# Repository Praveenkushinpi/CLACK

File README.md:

#  Thanks to HIGHWAY

```
 ________  ___       ________  ________  ___  __       
|\   ____\|\  \     |\   __  \|\   ____\|\  \|\  \     
\ \  \___|\ \  \    \ \  \|\  \ \  \___|\ \  \/  /|_   
 \ \  \    \ \  \    \ \   __  \ \  \    \ \   ___  \  
  \ \  \____\ \  \____\ \  \ \  \ \  \____\ \  \\ \  \ 
   \ \_______\ \_______\ \__\ \__\ \_______\ \__\\ \__\
    \|_______|\|_______|\|__|\|__|\|_______|\|__| \|__|

```

#  Clack — A Custom Mechanical Keyboard Build

Clack is a personal mechanical keyboard build crafted with a balance of sound, feel, and function — all under a budget of $150. Designed for a smooth typing experience and a clean aesthetic, Clack is as much a daily driver as it is a passion project.

---

##  Inspiration

The name **Clack** comes from the satisfying sound of tactile switches meeting carefully tuned stabilizers. Built for comfort and customizability, this keyboard is a love letter to DIY mechanical keyboard culture.

---

##  Build Overview

| Component     | Model/Brand               | Notes                          |
|---------------|----------------------------|--------------------------------|
| **Case**       | [Case](https://github.com/Praveenkushinpi/CLACK/tree/main/CASE)         | Material Plastic |
| **PCB**        | [PCB](https://github.com/Praveenkushinpi/CLACK/tree/main/PCB)          | Hot-swappable      |
| **Switches**   | [StacksKB](https://stackskb.com/store/akko-creamy-cyan-switch-pack-of-45-pre-order/)       | Soft/Clicky           |
| **Keycaps**    | [StacksKB](https://stackskb.com/store/wild-goose-keycaps/)         | Good              |

---

##  BOM

| Component     | Model/Brand               | Price                          |
|---------------|----------------------------|--------------------------------|
| **KeyCaps**       | [StacksKB](https://stackskb.com/store/akko-clear-white-keycap-set-v2-asa-profile/)         | 3999 inr = 50 usd |
| **Switches**        | [StacksKB](https://stackskb.com/store/akko-v3-crystal-pro-switch-pack-of-45/)          | 2999 inr = 35 usd       |
| **PCB**   | [JLCPCB](https://private-user-images.githubusercontent.com/168343716/456092456-044b7599-4a6e-40b4-bf12-a81c29c08c88.png?jwt=eyJhbGciOiJIUzI1NiIsInR5cCI6IkpXVCJ9.eyJpc3MiOiJnaXRodWIuY29tIiwiYXVkIjoicmF3LmdpdGh1YnVzZXJjb250ZW50LmNvbSIsImtleSI6ImtleTUiLCJleHAiOjE3NTA4MTkwNTksIm5iZiI6MTc1MDgxODc1OSwicGF0aCI6Ii8xNjgzNDM3MTYvNDU2MDkyNDU2LTA0NGI3NTk5LTRhNmUtNDBiNC1iZjEyLWE4MWMyOWMwOGM4OC5wbmc_WC1BbXotQWxnb3JpdGhtPUFXUzQtSE1BQy1TSEEyNTYmWC1BbXotQ3JlZGVudGlhbD1BS0lBVkNPRFlMU0E1M1BRSzRaQSUyRjIwMjUwNjI1JTJGdXMtZWFzdC0xJTJGczMlMkZhd3M0X3JlcXVlc3QmWC1BbXotRGF0ZT0yMDI1MDYyNVQwMjMyMzlaJlgtQW16LUV4cGlyZXM9MzAwJlgtQW16LVNpZ25hdHVyZT05ZDljN2U2ZmYwODhlZGU2OTJjNWVkYzk5MDk5ZWU5ODViZTY4NGQ2ZmY0Y2EyOGE5MThlMDdhMTg2MDMwMDdiJlgtQW16LVNpZ25lZEhlYWRlcnM9aG9zdCJ9.TJexbJ2JOPTNS0pWK4Fx8X82fOrmfui8mHUvjtpRxs8)       | 33 usd            |
| **Encoder**| [Robu.in](https://private-user-images.githubusercontent.com/168343716/456093939-859af2b1-9a2c-4d81-b4bb-97766db01e42.png?jwt=eyJhbGciOiJIUzI1NiIsInR5cCI6IkpXVCJ9.eyJpc3MiOiJnaXRodWIuY29tIiwiYXVkIjoicmF3LmdpdGh1YnVzZXJjb250ZW50LmNvbSIsImtleSI6ImtleTUiLCJleHAiOjE3NTA4MTkwNTksIm5iZiI6MTc1MDgxODc1OSwicGF0aCI6Ii8xNjgzNDM3MTYvNDU2MDkzOTM5LTg1OWFmMmIxLTlhMmMtNGQ4MS1iNGJiLTk3NzY2ZGIwMWU0Mi5wbmc_WC1BbXotQWxnb3JpdGhtPUFXUzQtSE1BQy1TSEEyNTYmWC1BbXotQ3JlZGVudGlhbD1BS0lBVkNPRFlMU0E1M1BRSzRaQSUyRjIwMjUwNjI1JTJGdXMtZWFzdC0xJTJGczMlMkZhd3M0X3JlcXVlc3QmWC1BbXotRGF0ZT0yMDI1MDYyNVQwMjMyMzlaJlgtQW16LUV4cGlyZXM9MzAwJlgtQW16LVNpZ25hdHVyZT1iMjA1NjJkOTMwMDA1N2Q3Yjk3ZTg1NjQ1ODc0OTgwYmY4NDY5NWFmMGJjYzkwMTY2NjUyZDFiYjYzNjExNmUxJlgtQW16LVNpZ25lZEhlYWRlcnM9aG9zdCJ9.BMnRanZ30tjBzOlprUQU22twroIURjnTTjO-QSRDdCs)  | 1 usd              |
| **Display**  | [Robu.in](https://private-user-images.githubusercontent.com/168343716/456094220-fea9dac9-632d-493f-b6a2-2cf06fdc8523.png?jwt=eyJhbGciOiJIUzI1NiIsInR5cCI6IkpXVCJ9.eyJpc3MiOiJnaXRodWIuY29tIiwiYXVkIjoicmF3LmdpdGh1YnVzZXJjb250ZW50LmNvbSIsImtleSI6ImtleTUiLCJleHAiOjE3NTA4MTkwNTksIm5iZiI6MTc1MDgxODc1OSwicGF0aCI6Ii8xNjgzNDM3MTYvNDU2MDk0MjIwLWZlYTlkYWM5LTYzMmQtNDkzZi1iNmEyLTJjZjA2ZmRjODUyMy5wbmc_WC1BbXotQWxnb3JpdGhtPUFXUzQtSE1BQy1TSEEyNTYmWC1BbXotQ3JlZGVudGlhbD1BS0lBVkNPRFlMU0E1M1BRSzRaQSUyRjIwMjUwNjI1JTJGdXMtZWFzdC0xJTJGczMlMkZhd3M0X3JlcXVlc3QmWC1BbXotRGF0ZT0yMDI1MDYyNVQwMjMyMzlaJlgtQW16LUV4cGlyZXM9MzAwJlgtQW16LVNpZ25hdHVyZT03NzIxYWFlODJjOTZiZWYwY2E0NmZmZGJmMmQwNjM2NDA0ZjEzMjBmODQ1ZTkyZTU0YzNjNGMyYWIyODY4YmJmJlgtQW16LVNpZ25lZEhlYWRlcnM9aG9zdCJ9.4TZm8LEaH7tvJQlJOL3LapiQ1uNSj3NfFEgdTf9ja4k)    | 3 usd            |

---

##  Features

- Split Keyboard
- must have 1 knobs
- a led screen
- work for both mac and windows devices
- Hot swappable 

---

##  Build Log / Showcase

---

##  Future Plans

- Swap to silent linear switches for nighttime use  
- Design custom keycap set with a "Clack" theme  
- Integrate rotary encoder or OLED screen
- Also planning to work on the split deisgn
---

##   Thanks to HIGHWAY

---

---

> “Clack is not just a sound — it's a feeling.”

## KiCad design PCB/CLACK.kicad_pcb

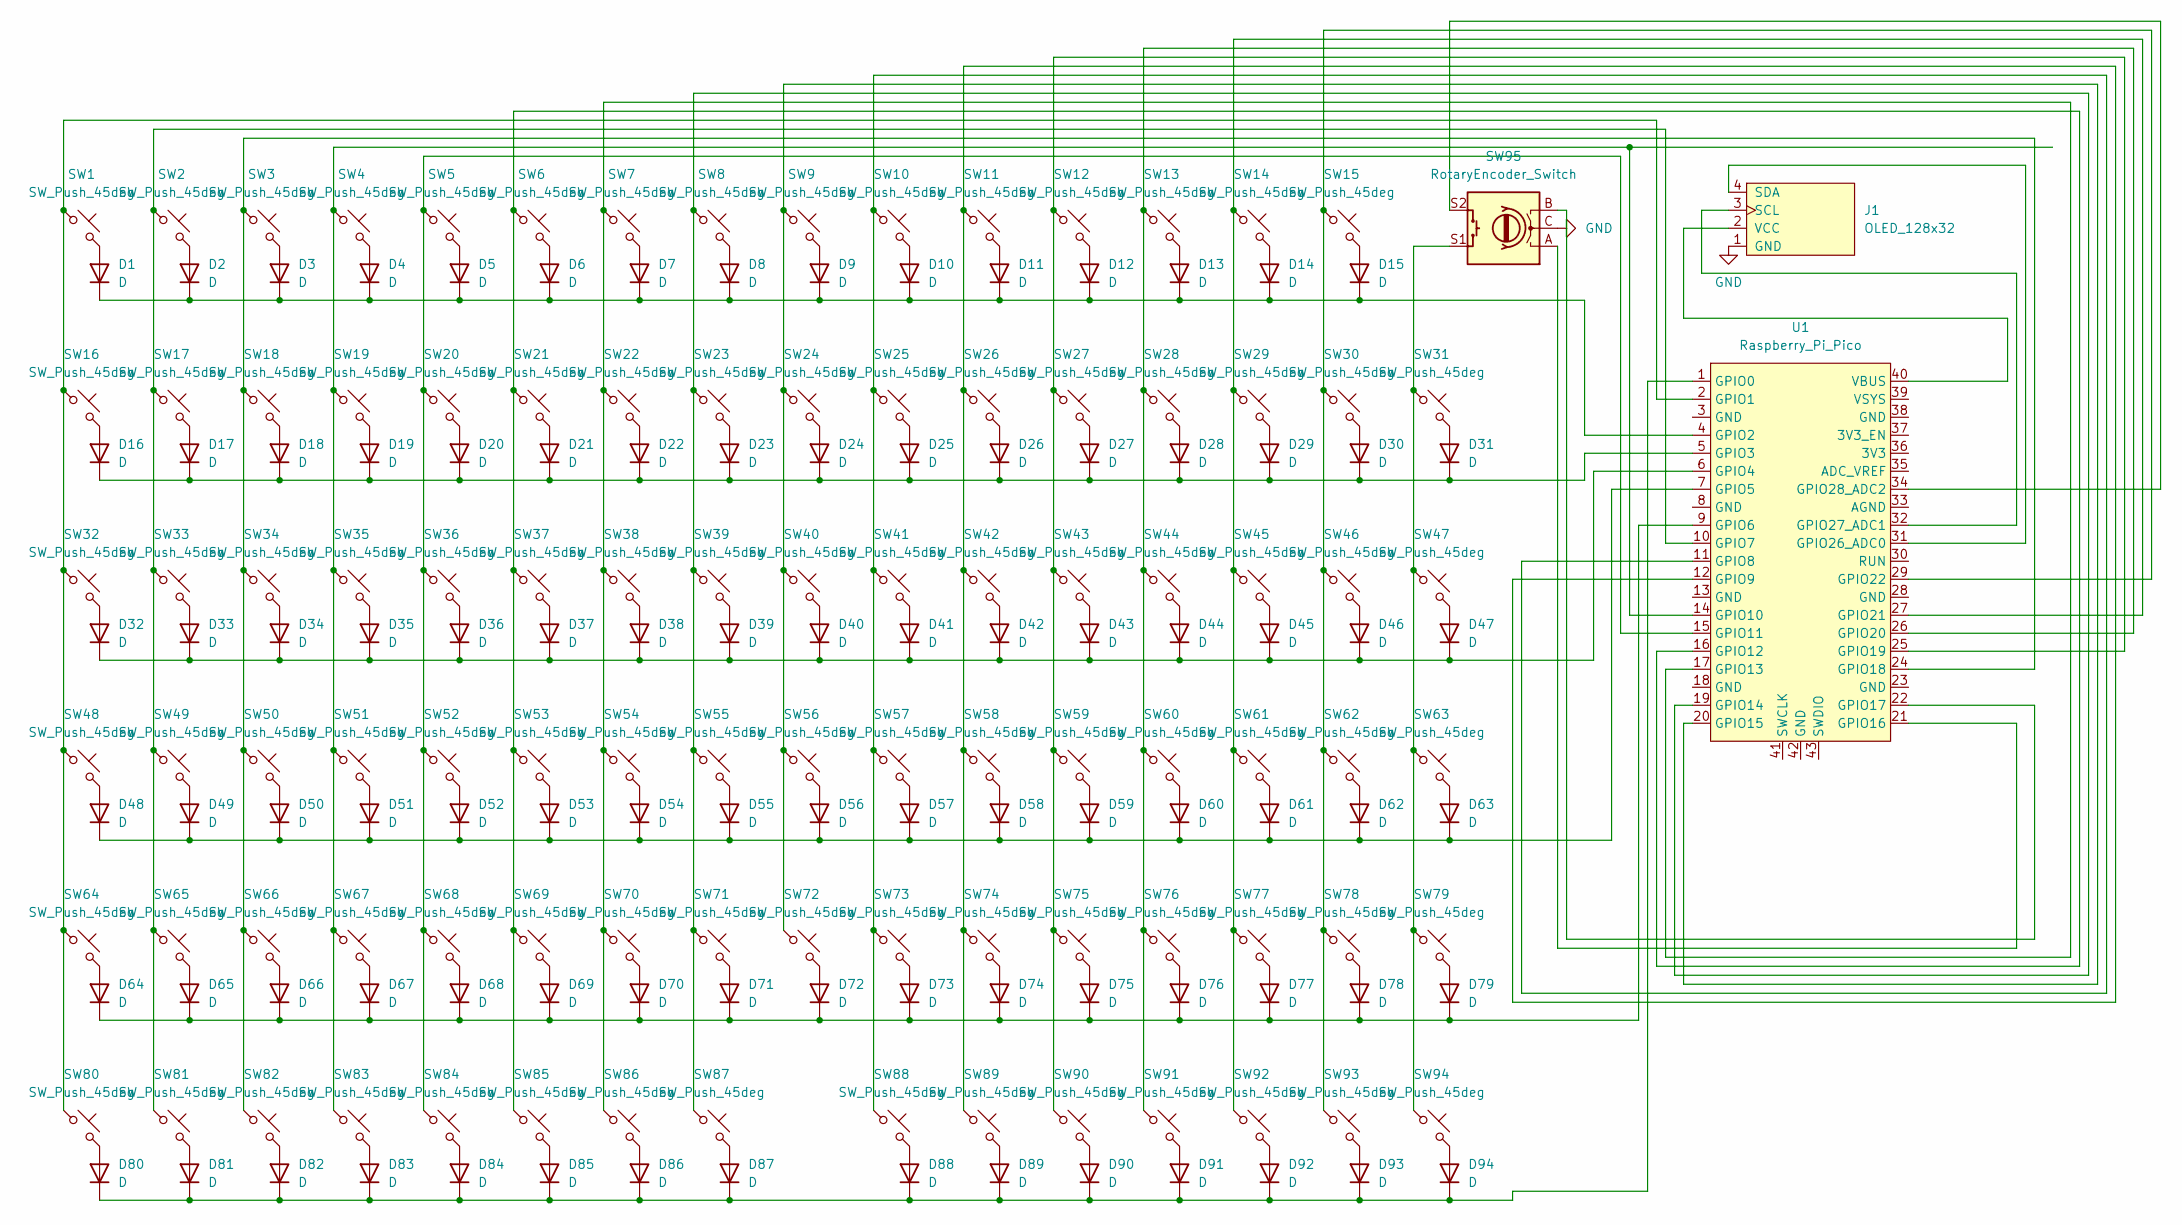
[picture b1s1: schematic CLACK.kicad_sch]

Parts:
D1, D2, D3, D4, D5, D6, D7, D8, D9, D10, D11, D12, D13, D14, D15, D16, D17, D18, D19, D20, D21, D22, D23, D24, D25, D26, D27, D28, D29, D30, D31, D32, D33, D34, D35, D36, D37, D38, D39, D40, D41, D42, D43, D44, D45, D46, D47, D48, D49, D50, D51, D52, D53, D54, D55, D56, D57, D58, D59, D60, D61, D62, D63, D64, D65, D66, D67, D68, D69, D70, D71, D72, D73, D74, D75, D76, D77, D78, D79, D80, D81, D82, D83, D84, D85, D86, D87, D88, D89, D90, D91, D92, D93, D94: D; Diode_SOD-123
J1: OLED_128x32
SW1, SW2, SW3, SW4, SW5, SW6, SW7, SW8, SW9, SW10, SW11, SW16, SW17, SW18, SW19, SW21, SW22, SW23, SW24, SW26, SW27, SW28, SW29, SW31, SW32, SW33, SW34, SW36, SW37, SW38, SW39, SW41, SW42, SW43, SW44, SW46, SW47, SW48, SW49, SW51, SW52, SW53, SW54, SW55, SW56, SW57, SW58, SW59, SW60, SW61, SW62, SW63, SW64, SW65, SW66, SW67, SW68, SW73, SW74, SW75, SW76, SW77, SW78, SW79, SW80, SW81, SW82, SW83, SW84, SW85, SW86, SW87, SW88, SW89, SW90, SW91, SW92, SW93, SW94: SW_Push_45deg; Hotswap_MX_1.00u
SW12, SW70: SW_Push_45deg; Hotswap_MX_1.50u
SW13: SW_Push_45deg; Hotswap_MX_1.75u
SW14, SW71: SW_Push_45deg; Hotswap_MX_2.25u
SW15, SW20, SW25, SW35, SW40, SW45, SW50: SW_Push_45deg; Hotswap_MX_1.25u
SW30: SW_Push_45deg; Hotswap_MX_6.25u
SW69: SW_Push_45deg; Hotswap_MX_2.00u
SW72: SW_Push_45deg; Hotswap_MX_2.75u
SW95: RotaryEncoder_Switch; RotaryEncoder_Alps_EC11E-Switch_Vertical_H20mm
U1: Raspberry_Pi_Pico

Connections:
GND: J1.1 (GND), SW95.C
unnamed: D1.2 (A), SW1.2
unnamed: D1.1 (K), D2.1 (K), D3.1 (K), D4.1 (K), D5.1 (K), D6.1 (K), D7.1 (K), D8.1 (K), D9.1 (K), D10.1 (K), D11.1 (K), D12.1 (K), D13.1 (K), D14.1 (K), D15.1 (K), U1.4 (GPIO2)
unnamed: D2.2 (A), SW2.2
unnamed: D3.2 (A), SW3.2
unnamed: D4.2 (A), SW4.2
unnamed: D5.2 (A), SW5.2
unnamed: D6.2 (A), SW6.2
unnamed: D7.2 (A), SW7.2
unnamed: D8.2 (A), SW8.2
unnamed: D9.2 (A), SW9.2
unnamed: D10.2 (A), SW10.2
unnamed: D11.2 (A), SW11.2
unnamed: D12.2 (A), SW12.2
unnamed: D13.2 (A), SW13.2
unnamed: D14.2 (A), SW14.2
unnamed: D15.2 (A), SW15.2
unnamed: D16.2 (A), SW16.2
unnamed: D16.1 (K), D17.1 (K), D18.1 (K), D19.1 (K), D20.1 (K), D21.1 (K), D22.1 (K), D23.1 (K), D24.1 (K), D25.1 (K), D26.1 (K), D27.1 (K), D28.1 (K), D29.1 (K), D30.1 (K), D31.1 (K), U1.5 (GPIO3)
unnamed: D17.2 (A), SW17.2
unnamed: D18.2 (A), SW18.2
unnamed: D19.2 (A), SW19.2
unnamed: D20.2 (A), SW20.2
unnamed: D21.2 (A), SW21.2
unnamed: D22.2 (A), SW22.2
unnamed: D23.2 (A), SW23.2
unnamed: D24.2 (A), SW24.2
unnamed: D25.2 (A), SW25.2
unnamed: D26.2 (A), SW26.2
unnamed: D27.2 (A), SW27.2
unnamed: D28.2 (A), SW28.2
unnamed: D29.2 (A), SW29.2
unnamed: D30.2 (A), SW30.2
unnamed: D31.2 (A), SW31.2
unnamed: D32.2 (A), SW32.2
unnamed: D32.1 (K), D33.1 (K), D34.1 (K), D35.1 (K), D36.1 (K), D37.1 (K), D38.1 (K), D39.1 (K), D40.1 (K), D41.1 (K), D42.1 (K), D43.1 (K), D44.1 (K), D45.1 (K), D46.1 (K), D47.1 (K), U1.6 (GPIO4)
unnamed: D33.2 (A), SW33.2
unnamed: D34.2 (A), SW34.2
unnamed: D35.2 (A), SW35.2
unnamed: D36.2 (A), SW36.2
unnamed: D37.2 (A), SW37.2
unnamed: D38.2 (A), SW38.2
unnamed: D39.2 (A), SW39.2
unnamed: D40.2 (A), SW40.2
unnamed: D41.2 (A), SW41.2
unnamed: D42.2 (A), SW42.2
unnamed: D43.2 (A), SW43.2
unnamed: D44.2 (A), SW44.2
unnamed: D45.2 (A), SW45.2
unnamed: D46.2 (A), SW46.2
unnamed: D47.2 (A), SW47.2
unnamed: D48.2 (A), SW48.2
unnamed: D48.1 (K), D49.1 (K), D50.1 (K), D51.1 (K), D52.1 (K), D53.1 (K), D54.1 (K), D55.1 (K), D56.1 (K), D57.1 (K), D58.1 (K), D59.1 (K), D60.1 (K), D61.1 (K), D62.1 (K), D63.1 (K), U1.7 (GPIO5)
unnamed: D49.2 (A), SW49.2
unnamed: D50.2 (A), SW50.2
unnamed: D51.2 (A), SW51.2
unnamed: D52.2 (A), SW52.2
unnamed: D53.2 (A), SW53.2
unnamed: D54.2 (A), SW54.2
unnamed: D55.2 (A), SW55.2
unnamed: D56.2 (A), SW56.2
unnamed: D57.2 (A), SW57.2
unnamed: D58.2 (A), SW58.2
unnamed: D59.2 (A), SW59.2
unnamed: D60.2 (A), SW60.2
unnamed: D61.2 (A), SW61.2
unnamed: D62.2 (A), SW62.2
unnamed: D63.2 (A), SW63.2
unnamed: D64.2 (A), SW64.2
unnamed: D64.1 (K), D65.1 (K), D66.1 (K), D67.1 (K), D68.1 (K), D69.1 (K), D70.1 (K), D71.1 (K), D72.1 (K), D73.1 (K), D74.1 (K), D75.1 (K), D76.1 (K), D77.1 (K), D78.1 (K), D79.1 (K), U1.9 (GPIO6)
unnamed: D65.2 (A), SW65.2
unnamed: D66.2 (A), SW66.2
unnamed: D67.2 (A), SW67.2
unnamed: D68.2 (A), SW68.2
unnamed: D69.2 (A), SW69.2
unnamed: D70.2 (A), SW70.2
unnamed: D71.2 (A), SW71.2
unnamed: D72.2 (A), SW72.2
unnamed: D73.2 (A), SW73.2
unnamed: D74.2 (A), SW74.2
unnamed: D75.2 (A), SW75.2
unnamed: D76.2 (A), SW76.2
unnamed: D77.2 (A), SW77.2
unnamed: D78.2 (A), SW78.2
unnamed: D79.2 (A), SW79.2
unnamed: D80.2 (A), SW80.2
unnamed: D80.1 (K), D81.1 (K), D82.1 (K), D83.1 (K), D84.1 (K), D85.1 (K), D86.1 (K), D87.1 (K), D88.1 (K), D89.1 (K), D90.1 (K), D91.1 (K), D92.1 (K), D93.1 (K), D94.1 (K), U1.1 (GPIO0)
unnamed: D81.2 (A), SW81.2
unnamed: D82.2 (A), SW82.2
unnamed: D83.2 (A), SW83.2
unnamed: D84.2 (A), SW84.2
unnamed: D85.2 (A), SW85.2
unnamed: D86.2 (A), SW86.2
unnamed: D87.2 (A), SW87.2
unnamed: D88.2 (A), SW88.2
unnamed: D89.2 (A), SW89.2
unnamed: D90.2 (A), SW90.2
unnamed: D91.2 (A), SW91.2
unnamed: D92.2 (A), SW92.2
unnamed: D93.2 (A), SW93.2
unnamed: D94.2 (A), SW94.2
unnamed: J1.3 (SCL), U1.32 (GPIO27_ADC1)
unnamed: J1.4 (SDA), U1.31 (GPIO26_ADC0)
unnamed: J1.2 (VCC), U1.40 (VBUS)
unnamed: SW31.1, SW47.1, SW63.1, SW79.1, SW94.1, SW95.S1
unnamed: SW1.1, SW16.1, SW32.1, SW48.1, SW64.1, SW80.1, U1.2 (GPIO1)
unnamed: SW2.1, SW17.1, SW33.1, SW49.1, SW65.1, SW81.1, U1.10 (GPIO7)
unnamed: SW10.1, SW25.1, SW41.1, SW57.1, SW73.1, SW88.1, U1.11 (GPIO8)
unnamed: SW11.1, SW26.1, SW42.1, SW58.1, SW74.1, SW89.1, U1.12 (GPIO9)
unnamed: SW4.1, SW19.1, SW35.1, SW51.1, SW67.1, SW83.1, U1.14 (GPIO10)
unnamed: SW5.1, SW20.1, SW36.1, SW52.1, SW68.1, SW84.1, U1.15 (GPIO11)
unnamed: SW6.1, SW21.1, SW37.1, SW53.1, SW69.1, SW85.1, U1.16 (GPIO12)
unnamed: SW7.1, SW22.1, SW38.1, SW54.1, SW70.1, SW86.1, U1.17 (GPIO13)
unnamed: SW8.1, SW23.1, SW39.1, SW55.1, SW71.1, SW87.1, U1.19 (GPIO14)
unnamed: SW9.1, SW24.1, SW40.1, SW56.1, SW72.1, U1.20 (GPIO15)
unnamed: SW95.A, U1.21 (GPIO16)
unnamed: SW95.B, U1.22 (GPIO17)
unnamed: SW3.1, SW18.1, SW34.1, SW50.1, SW66.1, SW82.1, U1.24 (GPIO18)
unnamed: SW12.1, SW27.1, SW43.1, SW59.1, SW75.1, SW90.1, U1.25 (GPIO19)
unnamed: SW13.1, SW28.1, SW44.1, SW60.1, SW76.1, SW91.1, U1.26 (GPIO20)
unnamed: SW14.1, SW29.1, SW45.1, SW61.1, SW77.1, SW92.1, U1.27 (GPIO21)
unnamed: SW15.1, SW30.1, SW46.1, SW62.1, SW78.1, SW93.1, U1.29 (GPIO22)
unnamed: SW95.S2, U1.34 (GPIO28_ADC2)

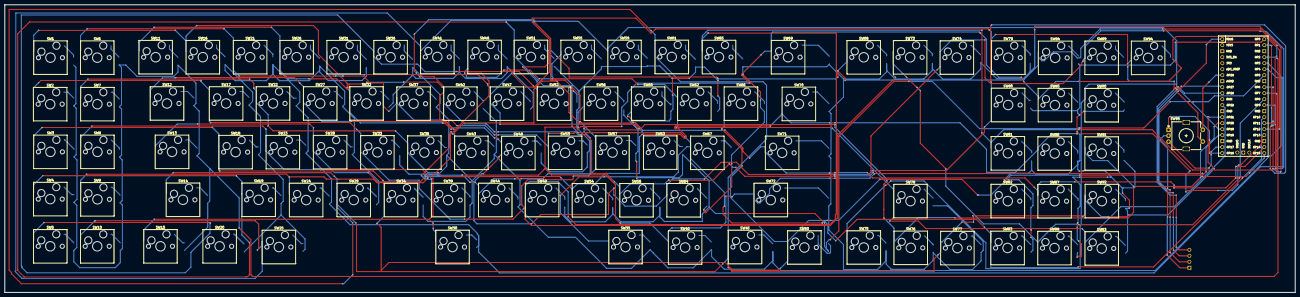
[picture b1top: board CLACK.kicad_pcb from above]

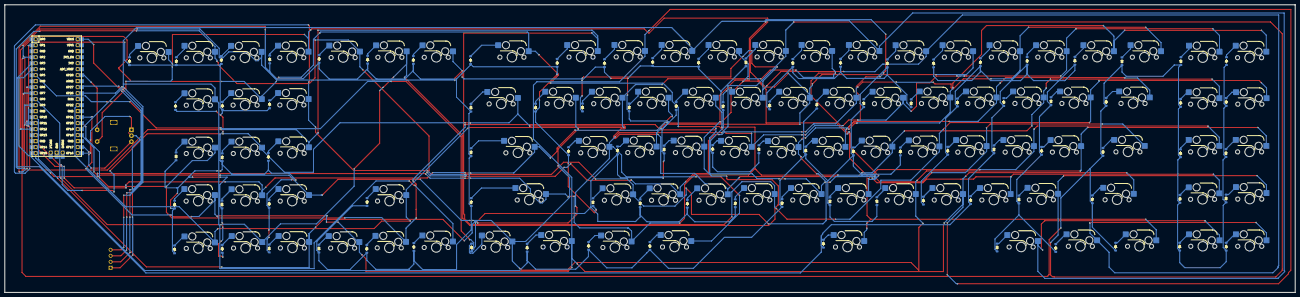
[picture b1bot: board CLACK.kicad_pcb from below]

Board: 2 copper layers, 546.6 x 121.9 mm, 191 parts (95 on the bottom side), 123 nets.

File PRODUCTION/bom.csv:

Designator,Footprint,Quantity,Value,LCSC Part #
"D1, D10, D11, D12, D13, D14, D15, D16, D17, D18, D19, D2, D20, D21, D22, D23, D24, D25, D26, D27, D28, D29, D3, D30, D31, D32, D33, D34, D35, D36, D37, D38, D39, D4, D40, D41, D42, D43, D44, D45, D46, D47, D48, D49, D5, D50, D51, D52, D53, D54, D55, D56, D57, D58, D59, D6, D60, D61, D62, D63, D64, D65, D66, D67, D68, D69, D7, D70, D71, D72, D73, D74, D75, D76, D77, D78, D79, D8, D80, D81, D82, D83, D84, D85, D86, D87, D88, D89, D9, D90, D91, D92, D93, D94",Diode_SOD-123,94,D,
J1,OLED_128x32,1,OLED_128x32,
"SW1, SW10, SW11, SW16, SW17, SW18, SW19, SW2, SW21, SW22, SW23, SW24, SW26, SW27, SW28, SW29, SW3, SW31, SW32, SW33, SW34, SW36, SW37, SW38, SW39, SW4, SW41, SW42, SW43, SW44, SW46, SW47, SW48, SW49, SW5, SW51, SW52, SW53, SW54, SW55, SW56, SW57, SW58, SW59, SW6, SW60, SW61, SW62, SW63, SW64, SW65, SW66, SW67, SW68, SW7, SW73, SW74, SW75, SW76, SW77, SW78, SW79, SW8, SW80, SW81, SW82, SW83, SW84, SW85, SW86, SW87, SW88, SW89, SW9, SW90, SW91, SW92, SW93, SW94",Hotswap_MX_1.00u,79,SW_Push_45deg,
"SW12, SW70",Hotswap_MX_1.50u,2,SW_Push_45deg,
SW13,Hotswap_MX_1.75u,1,SW_Push_45deg,
"SW14, SW71",Hotswap_MX_2.25u,2,SW_Push_45deg,
"SW15, SW20, SW25, SW35, SW40, SW45, SW50",Hotswap_MX_1.25u,7,SW_Push_45deg,
SW30,Hotswap_MX_6.25u,1,SW_Push_45deg,
SW69,Hotswap_MX_2.00u,1,SW_Push_45deg,
SW72,Hotswap_MX_2.75u,1,SW_Push_45deg,
SW95,RotaryEncoder_Alps_EC11E-Switch_Vertical_H20mm,1,RotaryEncoder_Switch,
U1,Raspberry_Pi_Pico,1,Raspberry_Pi_Pico,

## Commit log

2025-06-17 Create nil
2025-08-29 Update switch description from 'Tactile' to 'Soft'
2025-08-29 Mention split design plans in README
